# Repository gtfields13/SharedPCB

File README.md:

# SharedPCB
Phido Sound PCBs that are freely shared for others to leverage or use.

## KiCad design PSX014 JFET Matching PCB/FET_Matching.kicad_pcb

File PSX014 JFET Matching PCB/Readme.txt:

PCB design extending the @gadgetreboot JFET tester to add a switch for approximating Vgs(off) using 10M resistor.

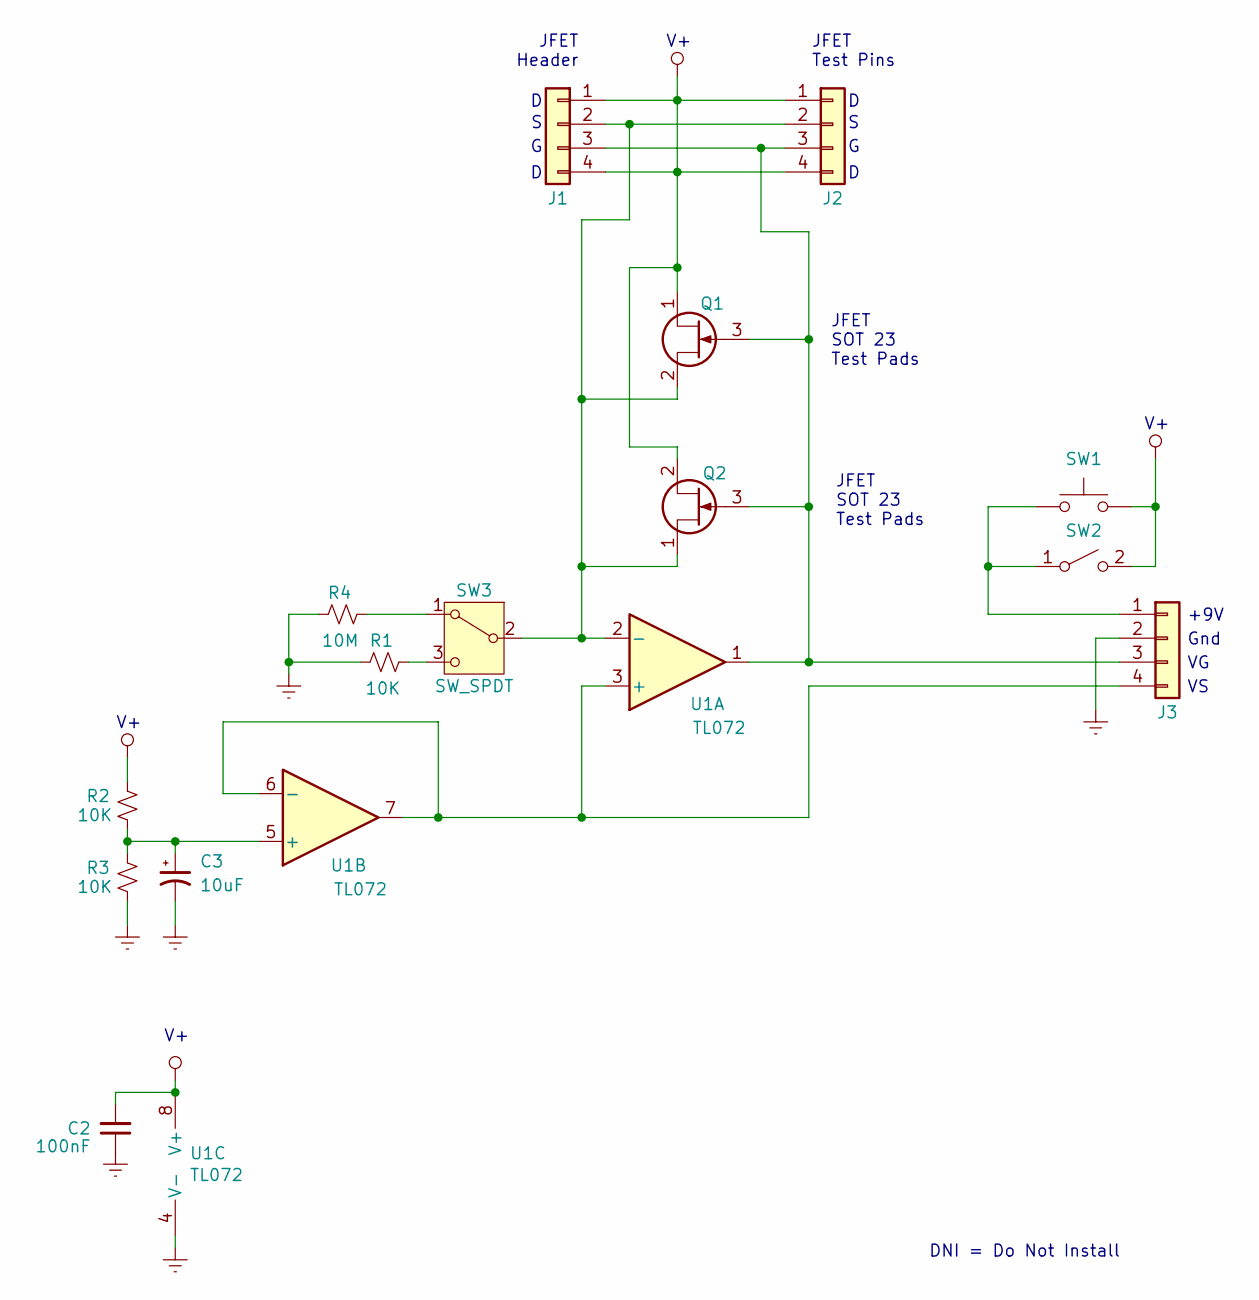
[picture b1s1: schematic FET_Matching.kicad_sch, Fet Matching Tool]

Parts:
C2: 100nF; C_Disc_D3.4mm_W2.1mm_P2.50mm
C3: 10uF; CP_Radial_D5.0mm_P2.50mm
J1, J2, J3: Conn_01x04; PinHeader_1x04_P2.54mm_Vertical
Q1: BSR56; SOT-23
Q2: BF545C; SOT-23
R1, R2, R3: 10K; R_Axial_DIN0309_L9.0mm_D3.2mm_P12.70mm_Horizontal
R4: 10M; R_Axial_DIN0309_L9.0mm_D3.2mm_P12.70mm_Horizontal
SW1: SW_Push; PushButton
SW2: SW_SPST; SPDT.LUGS
SW3: SW_SPDT; SPDT.LUGS
U1: TL072; DIP-8_W7.62mm

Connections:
GNDREF: C2.1, C3.2, J3.2, R1.2, R3.2, R4.2, U1.4 (V-)
unnamed: J1.2, J2.2, Q1.2 (S), Q2.1 (S), SW3.2 (B), U1.2 (-)
unnamed: J1.3, J2.3, J3.3, Q1.3 (G), Q2.3 (G), U1.1
unnamed: J3.1, SW1.1, SW2.1 (A)
unnamed: J3.4, U1.3 (+), U1.6 (-), U1.7
unnamed: R4.1, SW3.1 (A)
unnamed: R1.1, SW3.3 (C)
unnamed: C3.1, R2.2, R3.1, U1.5 (+)
VCC: C2.2, J1.1, J1.4, J2.1, J2.4, Q1.1 (D), Q2.2 (D), R2.1, SW1.2, SW2.2 (B), U1.8 (V+)

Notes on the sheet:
+9V
JFET SOT 23 Test Pads
Gnd
JFET Test Pins
JFET Header
DNI = Do Not Install

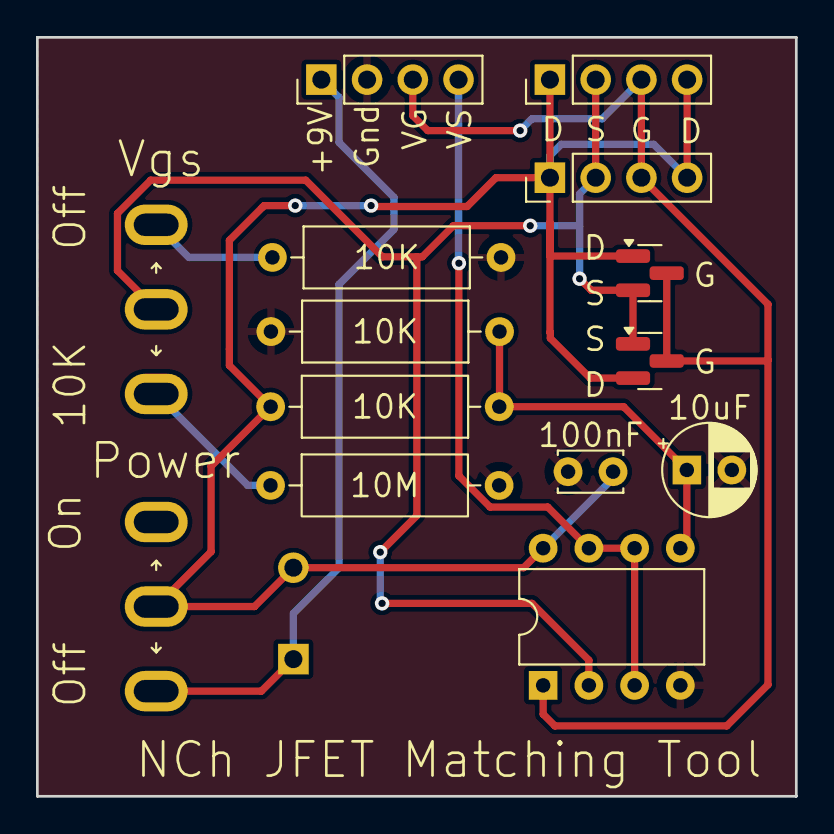
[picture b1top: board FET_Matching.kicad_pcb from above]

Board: 2 copper layers, 42.2 x 42.2 mm, 15 parts (0 on the bottom side), 9 nets.

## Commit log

2025-11-12 Create PSX005_Neutrik_M_PCB_with_JST-XH
2026-03-06 Add files via upload
    PCB for building a JFET test tool to measure Vgs(10K) and Vgs (off). Vgs off approximated by using 10M resistor
